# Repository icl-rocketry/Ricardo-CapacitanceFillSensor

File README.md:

# Ricardo-CapacitanceFillSensor

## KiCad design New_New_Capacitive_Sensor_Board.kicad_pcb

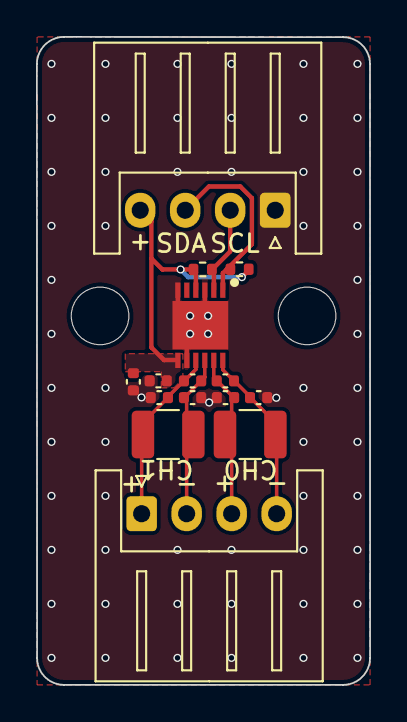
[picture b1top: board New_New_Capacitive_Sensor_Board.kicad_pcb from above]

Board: 2 copper layers, 18.5 x 36.0 mm, 17 parts (0 on the bottom side), 8 nets.

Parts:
C3, C4: 33p; C_0402_1005Metric
C5, C6, C7, C8: 18p; C_0402_1005Metric
C9: 0.1u; C_0402_1005Metric
C10: 1u; C_0402_1005Metric
H1, H2: MountingHole; MountingHole_3.2mm_M3_DIN965
IC1: FDC2212QDNTTQ1; SON50P400X400X100-13N
J1, J2: Conn_01x04_Pin; JST_XH_S4B-XH-A_1x04_P2.50mm_Horizontal
L1, L2: 18u; L_1210_3225Metric
R3, R4: 1k; R_0402_1005Metric

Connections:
GND: C5.2, C6.1, C7.2, C8.1, C9.2, C10.2, IC1.3 (CLKIN), IC1.6 (SD), IC1.8 (GND), IC1.13 (DAP), J1.1
IN0+: C3.1, C5.1, IC1.9 (IN0A), J2.1, L1.1
IN0-: C3.2, C6.2, IC1.10 (IN0B), J2.2, L1.2
IN1+: C4.1, C7.1, IC1.11 (IN1A), J2.3, L2.1
IN1-: C4.2, C8.2, IC1.12 (IN1B), J2.4, L2.2
SCL: IC1.1 (SCL), J1.3, R3.2
SDA: IC1.2 (SDA), J1.2, R4.2
VDD: C9.1, C10.1, IC1.4 (ADDR), IC1.7 (VDD), J1.4, R3.1, R4.1

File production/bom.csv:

Designator,Footprint,Quantity,Value,LCSC Part #
C10,0402,1,1u,
"C3, C4",0402,2,33p,
"C5, C6, C7, C8",0402,4,18p,
C9,0402,1,0.1u,
IC1,SON50P400X400X100-13N,1,FDC2212QDNTTQ1,
J1,Molex_Nano-Fit_105313-xx04_1x04_P2.50mm_Horizontal,1,Conn_01x04_Pin,
"J3, J4",Molex_Nano-Fit_105313-xx02_1x02_P2.50mm_Horizontal,2,Conn_01x02_Pin,
"L1, L2",1210,2,18u,
"R3, R4",0402,2,1k,

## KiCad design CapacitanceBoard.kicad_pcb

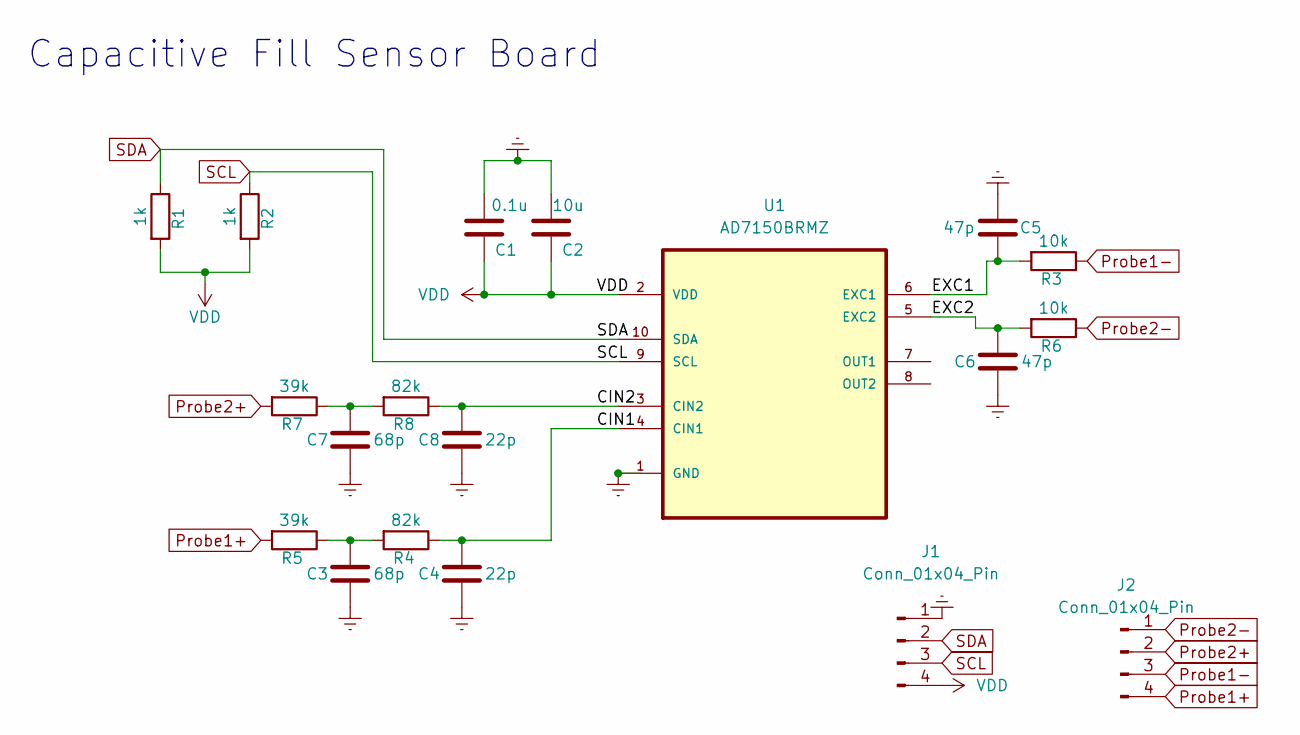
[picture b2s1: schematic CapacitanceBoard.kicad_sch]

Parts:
C1: 0.1u; C_0402_1005Metric
C2: 10u; C_0402_1005Metric
C3, C7: 68p; C_0402_1005Metric
C4, C8: 22p; C_0402_1005Metric
C5, C6: 47p; C_0402_1005Metric
J1, J2: Conn_01x04_Pin; JST_XH_S4B-XH-A_1x04_P2.50mm_Horizontal
R1, R2: 1k; R_0402_1005Metric
R3, R6: 10k; R_0402_1005Metric
R4, R8: 82k; R_0402_1005Metric
R5, R7: 39k; R_0402_1005Metric
U1: AD7150BRMZ; SOP50P490X110-10N; MPN AD7150BRMZ

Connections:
/CIN1: C4.1, R4.1, U1.4 (CIN1)
/CIN2: C8.1, R8.1, U1.3 (CIN2)
/EXC1: C5.1, R3.2, U1.6 (EXC1)
/EXC2: C6.1, R6.2, U1.5 (EXC2)
Earth: C1.2, C2.2, C3.2, C4.2, C5.2, C6.2, C7.2, C8.2, J1.1, U1.1 (GND)
unnamed: C3.1, R4.2, R5.1
unnamed: C7.1, R7.1, R8.2
Probe1+: J2.4, R5.2
Probe1-: J2.3, R3.1
Probe2+: J2.2, R7.2
Probe2-: J2.1, R6.1
SCL: J1.3, R2.1, U1.9 (SCL)
SDA: J1.2, R1.1, U1.10 (SDA)
VDD: C1.1, C2.1, J1.4, R1.2, R2.2, U1.2 (VDD)

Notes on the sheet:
Capacitive Fill Sensor Board

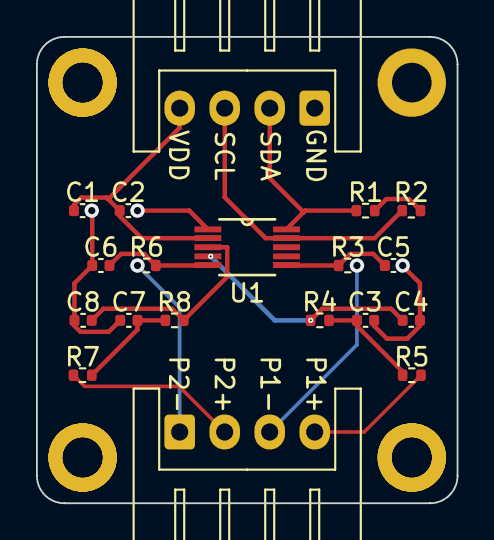
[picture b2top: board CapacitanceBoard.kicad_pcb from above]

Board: 2 copper layers, 23.4 x 25.9 mm, 19 parts (0 on the bottom side), 14 nets.

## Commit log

2023-11-11 Added PCB and Schematic Files
2023-11-11 Added Connectors to PCB
2023-11-12 Added Decoupling Capacitor.
2023-11-14 Added Mounting Holes
2023-11-14 Changed Connector Type to JST-XH
2023-11-14 Added Second Decoupling Cap
2023-11-14 Added Pull-Up Resistors.
2023-11-14 Added EMI Filtering.
2023-12-12 Added Schematic Files
2024-01-21 Improved schematic and updated PCB references and layout.
2024-02-02 Added Second Probe Input
2024-03-01 Made new schem. and pcb for spec changes
2024-03-28 Schematic changes specified in design review
2024-03-29 Update PCB Design as per Design Review
2024-03-30 Remove harsh trace angles
2024-04-28 needs gerber files
2024-04-28 Changed to nanofits and ordering stuff
